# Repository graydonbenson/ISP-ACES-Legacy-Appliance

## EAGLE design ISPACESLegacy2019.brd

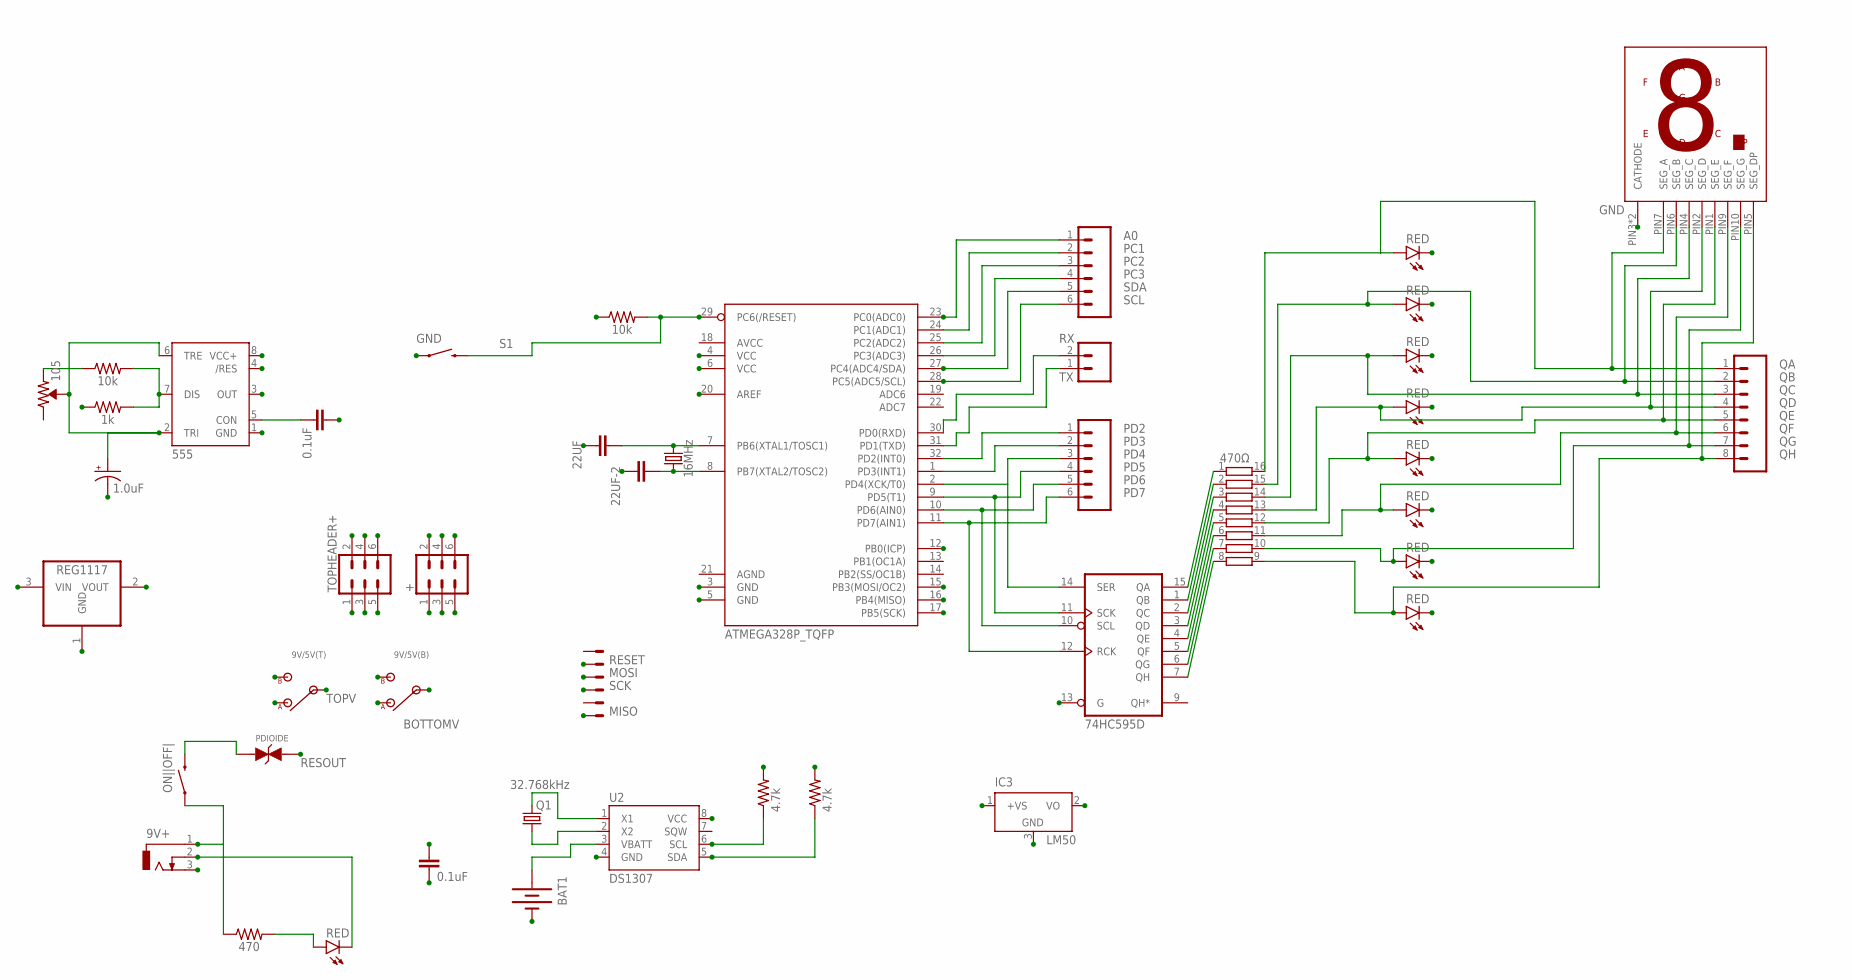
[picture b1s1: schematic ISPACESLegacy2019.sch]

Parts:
9V+: DCJ0202
9V/5V(B), 9V/5V(T): RES_SWITCH
22UF, 22UF-2: 22UF-1210-16V-20%; 1210
470Ω: 2NBS16-8; SO16
+: CONN_03X22X3_SILK_MALE_PTH; 2X3
BAT1: BATTERY12PTH; BATTCON_12MM_PTH
C3: 0.1uF; 0603-CAP
C4: 0.1uF; 0603
C5: 1.0uF; EIA3216
D1, D2, D3, D4, D5, D6, D7, D8, D10: RED; LED-1206
IC1: 74HC595D; SO16
IC2: 555; SO08
IC3: LM50; SOT23
IC4: REG1117; SOT223
ISP: 52745-0690
J1: CONN_08BM08B-SRSS-TB; BM08B-SRSS-TB
J2: CONN_02-JST-2MM-SMT; JST-2-SMD
J4, J5: CONN_06SMD-FEMALE-V2; 1X06-SMD-FEMALE
ON||OFF|: RS032G05A3SM-SPST-MOMENTARY-SWSMD-1101NE; TACTILE-SWITCH-1101NE
PDIOIDE: WE-TVSP_BI_600W_824521201; VARTVSP_SMB/DO-214AA
Q1: 32.768kHz; CRYSTAL-32KHZ-SMD
R2: 470; 0603
R3, R4: 4.7k; 0603
R5, R7: 10k; 0603
R6: 1k; 0603
S1: MOMENTARY-SWITCH-SPST-SMD-6.2MM-TALL; TACTILE_SWITCH_SMD_6.2MM_TALL
TOPHEADER+: CONN_03X22X3_SILK_MALE_PTH; 2X3
U2: DS1307; SO08-TIGHT
U4: ATMEGA328P_TQFP; TQFP32-08
U$1: ACSC56SMT; ACSC56
VR1: 105; TRIMPOT-SMD-3MM-CLOSED
Y1: 16MHz; CRYSTAL-SMD-5X3.2-4PAD

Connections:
5V: 9V/5V(B).A, 9V/5V(T).A, C3.1, IC2.4 (/RES), IC2.8 (VCC+), IC3.1 (+VS), IC4.2 (VOUT), R3.2, R4.2, R5.1, R6.1, U2.8 (VCC), U4.4 (VCC), U4.6 (VCC), U4.20 (AREF)
A0: IC3.2 (VO), J4.1, U4.23 (PC0(ADC0))
BOTTOMV: 9V/5V(B).C (IN), +.2, +.4, +.6
GND: 9V+.2, 9V+.3, 22UF.2, 22UF-2.2, +.1, +.3, +.5, BAT1.GND (-), C3.2, C4.1, C5.-, D1.C, D2.C, D3.C, D4.C, D5.C, D6.C, D7.C, D8.C, D10.C, IC1.8 (GND), IC1.13 (G), IC2.1 (GND), IC3.3 (GND), IC4.1 (GND), S1.A2 (1), TOPHEADER+.1, TOPHEADER+.3, TOPHEADER+.5, U2.4 (GND), U4.3 (GND), U4.5 (GND), U$1.PIN3 (CATHODE), U$1.PIN8 (CATHODE)
MISO: ISP.6, U4.16 (PB4(MISO))
MOSI: ISP.3, U4.15 (PB3(MOSI/OC2))
unnamed: D10.A, R2.2
unnamed: 22UF.1, U4.7 (PB6(XTAL1/TOSC1)), Y1.3 (2)
unnamed: ON||OFF|.2, PDIOIDE.1
unnamed: 22UF-2.1, U4.8 (PB7(XTAL2/TOSC2)), Y1.1
unnamed: IC2.7 (DIS), R6.2, R7.2
unnamed: C5.+, IC2.2 (TRI), IC2.6 (TRE), VR1.2 (WIPER)
unnamed: Q1.X2 (2), U2.1 (X1)
unnamed: Q1.X1 (1), U2.2 (X2)
unnamed: BAT1.VCC@1 (+), U2.3 (VBATT)
unnamed: C4.2, IC2.5 (CON)
unnamed: 470Ω.1, IC1.15 (QA)
unnamed: 470Ω.2, IC1.1 (QB)
unnamed: 470Ω.3, IC1.2 (QC)
unnamed: 470Ω.4, IC1.3 (QD)
unnamed: 470Ω.5, IC1.4 (QE)
unnamed: 470Ω.6, IC1.5 (QF)
unnamed: 470Ω.7, IC1.6 (QG)
unnamed: 470Ω.8, IC1.7 (QH)
unnamed: R7.1, VR1.1 (CCW)
PB0: IC2.3 (OUT), U4.12 (PB0(ICP))
PC1: J4.2, U4.24 (PC1(ADC1))
PC2: J4.3, U4.25 (PC2(ADC2))
PC3: J4.4, U4.26 (PC3(ADC3))
PD2: J5.1, U4.32 (PD2(INT0))
PD3: J5.2, U4.1 (PD3(INT1))
PD4: IC1.14 (SER), J5.3, U4.2 (PD4(XCK/T0))
PD5: IC1.11 (SCK), J5.4, U4.9 (PD5(T1))
PD6: IC1.10 (SCL), J5.5, U4.10 (PD6(AIN0))
PD7: IC1.12 (RCK), J5.6, U4.11 (PD7(AIN1))
QA: 470Ω.16, D1.A, J1.1, U$1.PIN7 (SEG_A)
QB: 470Ω.15, D2.A, J1.2, U$1.PIN6 (SEG_B)
QC: 470Ω.14, D3.A, J1.3, U$1.PIN4 (SEG_C)
QD: 470Ω.13, D4.A, J1.4, U$1.PIN2 (SEG_D)
QE: 470Ω.12, D5.A, J1.5, U$1.PIN1 (SEG_E)
QF: 470Ω.11, D6.A, J1.6, U$1.PIN9 (SEG_F)
QG: 470Ω.10, D7.A, J1.7, U$1.PIN10 (SEG_G)
QH: 470Ω.9, D8.A, J1.8, U$1.PIN5 (SEG_DP)
RESET: ISP.2, R5.2, S1.B2 (2), U4.29 (PC6(/RESET))
RESOUT: 9V/5V(B).B, 9V/5V(T).B, IC4.3 (VIN), PDIOIDE.2
RX: J2.2 (1), U4.30 (PD0(RXD))
SCK: ISP.4, U4.17 (PB5(SCK))
SCL: J4.6, R3.1, U2.6 (SCL), U4.28 (PC5(ADC5/SCL))
SDA: J4.5, R4.1, U2.5 (SDA), U4.27 (PC4(ADC4/SDA))
TOPV: 9V/5V(T).C (IN), TOPHEADER+.2, TOPHEADER+.4, TOPHEADER+.6
TX: J2.1 (2), U4.31 (PD1(TXD))
UNRESOUT: 9V+.1, ON||OFF|.1, R2.1
VCC: IC1.16 (VCC)

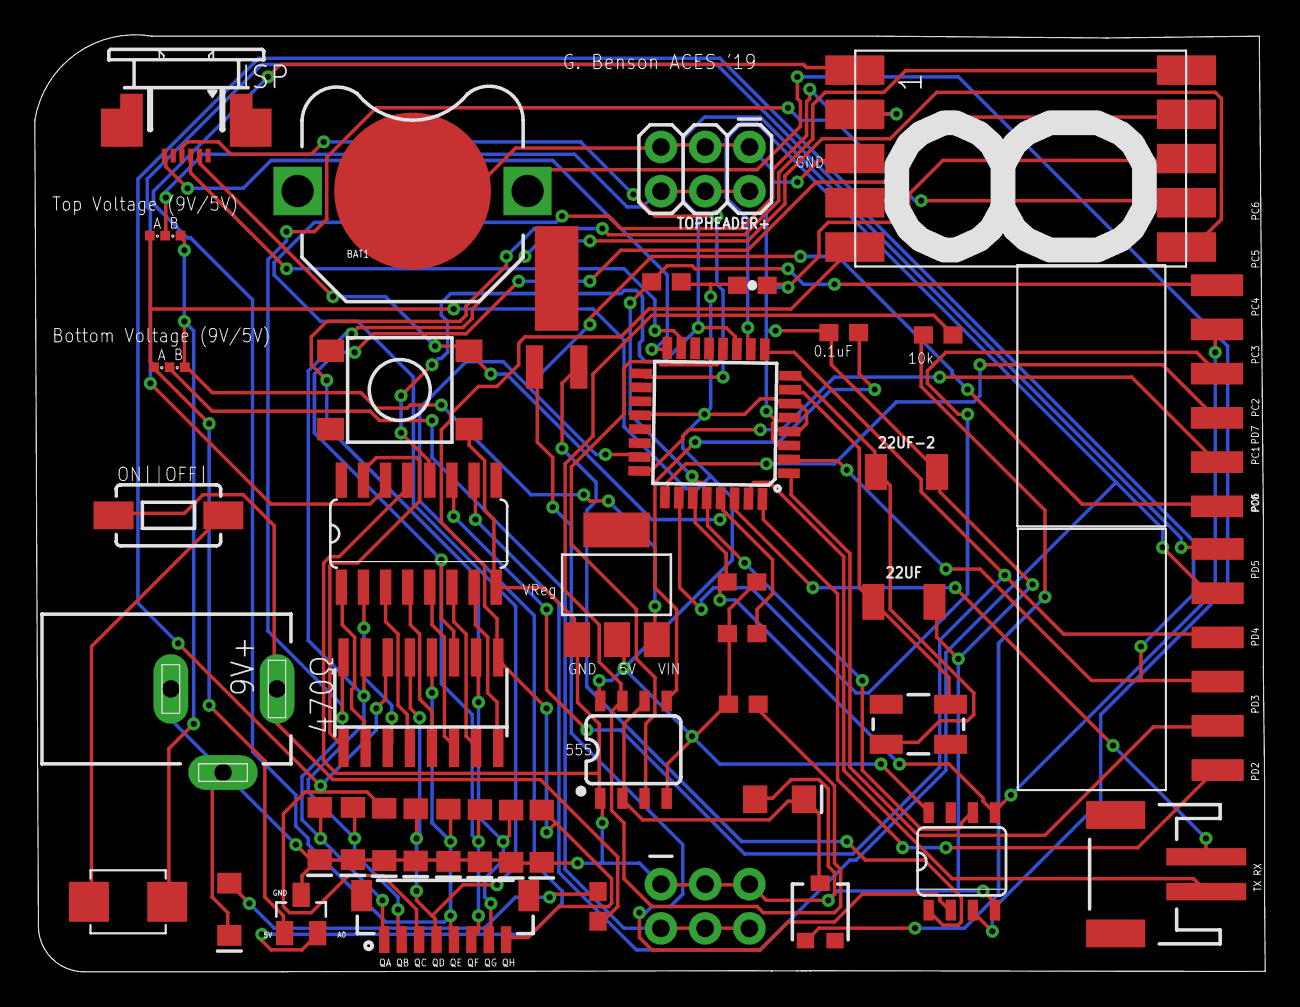
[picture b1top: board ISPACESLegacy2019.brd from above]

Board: 2 copper layers, 70.7 x 53.8 mm, 45 parts (1 on the bottom side), 52 nets.

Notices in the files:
parts and their libraries:
SparkFun-Connectors: Licensing: Creative Commons ShareAlike 4.0 International - https://creativecommons.org/licenses/by-sa/4.0
Wurth_Elektronik_Passive_rev18f: Copyright: Würth Elektronik
SparkFun-FreqCtrl: Licensing: CC v3.0 Share-Alike You are welcome to use this library for commercial purposes.
